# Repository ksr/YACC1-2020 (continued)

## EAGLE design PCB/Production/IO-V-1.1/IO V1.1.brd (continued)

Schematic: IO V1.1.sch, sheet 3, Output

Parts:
0, 1, 2, 3, 4, 5, 6, 7: LED5MM
HI: HTIL311A
IC4, IC9: 74273N; DIL20
IC6, IC11: 74LS10N; DIL14
IC7: 74LS00N; DIL14
LO: HTIL311A
OUT: LED5MM
R1, R3, R4, R5, R6, R7, R8, R9, R10: R-US_0207/10; 0207/10
TM1: 10k; TRIM-3386
X2: HD44780LCD-1602; LCD1602

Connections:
-B-RESET: IC4.1 (CLR), IC9.1 (CLR); also elsewhere on the board
DATA0: IC4.3 (D1), IC9.3 (D1), X2.7 (DB0); also elsewhere on the board
DATA1: IC4.4 (D2), IC9.4 (D2), X2.8 (DB1); also elsewhere on the board
DATA2: IC4.7 (D3), IC9.7 (D3), X2.9 (DB2); also elsewhere on the board
DATA3: IC4.8 (D4), IC9.8 (D4), X2.10 (DB3); also elsewhere on the board
DATA4: IC4.13 (D5), IC9.13 (D5), X2.11 (DB4); also elsewhere on the board
DATA5: IC4.14 (D6), IC9.14 (D6), X2.12 (DB5); also elsewhere on the board
DATA6: IC4.17 (D7), IC9.17 (D7), X2.13 (DB6); also elsewhere on the board
DATA7: IC4.18 (D8), IC9.18 (D8), X2.14 (DB7); also elsewhere on the board
GND: 0.K (C), 1.K (C), 2.K (C), 3.K (C), 4.K (C), 5.K (C), 6.K (C), 7.K (C), HI.5 (L-SI), HI.7 (GND), HI.8 (BI), IC4.10 (GND), IC6.7 (GND), IC7.7 (GND), IC9.10 (GND), IC11.7 (GND), LO.5 (L-SI), LO.7 (GND), LO.8 (BI), OUT.K (C), TM1.3 (E), X2.1 (VSS), X2.5 (RW), X2.16 (K); also elsewhere on the board
IO-SELDATA: IC6.2 (I1), IC6.9 (I0), IC11.2 (I1); also elsewhere on the board
IO-WR: IC6.1 (I0), IC6.11 (I2), IC11.1 (I0); also elsewhere on the board
LCD-ENABLE: IC6.10 (I1); also elsewhere on the board
LCD-REGISTER: X2.4 (RS); also elsewhere on the board
unnamed: OUT.A, R1.1
unnamed: 2.A, R5.1
unnamed: 3.A, R6.1
unnamed: 4.A, R7.1
unnamed: 0.A, R3.1
unnamed: 1.A, R4.1
unnamed: 5.A, R8.1
unnamed: 7.A, R10.1
unnamed: 6.A, R9.1
unnamed: IC4.19 (Q8), R10.2
unnamed: IC4.16 (Q7), R9.2
unnamed: IC4.15 (Q6), R8.2
unnamed: IC4.12 (Q5), R7.2
unnamed: IC4.9 (Q4), R6.2
unnamed: IC4.6 (Q3), R5.2
unnamed: IC4.5 (Q2), R4.2
unnamed: IC4.2 (Q1), R3.2
unnamed: HI.12 (D3), IC9.19 (Q8)
unnamed: IC7.3 (O), X2.6 (E)
unnamed: IC6.8 (O), IC7.1 (I0), IC7.2 (I1)
unnamed: IC4.11 (CLK), IC6.12 (O)
unnamed: TM1.2 (S), X2.3 (VO)
unnamed: HI.13 (D2), IC9.16 (Q7)
unnamed: HI.2 (D1), IC9.15 (Q6)
unnamed: HI.3 (D0), IC9.12 (Q5)
unnamed: IC9.9 (Q4), LO.12 (D3)
unnamed: IC9.6 (Q3), LO.13 (D2)
unnamed: IC9.5 (Q2), LO.2 (D1)
unnamed: IC9.2 (Q1), LO.3 (D0)
unnamed: IC9.11 (CLK), IC11.12 (O)
OUT: R1.2; also elsewhere on the board
SWITCH-LED: IC6.13 (I2); also elsewhere on the board
TIL311: IC11.13 (I2); also elsewhere on the board
VCC: HI.1 (LEDSUP), HI.14 (VCC), IC4.20 (VCC), IC6.14 (VCC), IC7.14 (VCC), IC9.20 (VCC), IC11.14 (VCC), LO.1 (LEDSUP), LO.14 (VCC), TM1.1 (A), X2.2 (VDD), X2.15 (A); also elsewhere on the board

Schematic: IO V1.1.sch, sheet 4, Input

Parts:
IC3: 74LS244N; DIL20
IC6: 74LS10N; DIL14
IN: M9040P
INPUT: PINHD-1X2; 1X02
S0, S1, S2, S3, S4, S5, S6, S7: M9040P

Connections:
DATA0: IC3.18 (Y1); also elsewhere on the board
DATA1: IC3.16 (Y2); also elsewhere on the board
DATA2: IC3.14 (Y3); also elsewhere on the board
DATA3: IC3.12 (Y4); also elsewhere on the board
DATA4: IC3.9 (Y1); also elsewhere on the board
DATA5: IC3.7 (Y2); also elsewhere on the board
DATA6: IC3.5 (Y3); also elsewhere on the board
DATA7: IC3.3 (Y4); also elsewhere on the board
GND: IC3.10 (GND), IC6.7 (GND), IN.3 (S), S0.3 (S), S1.3 (S), S2.3 (S), S3.3 (S), S4.3 (S), S5.3 (S), S6.3 (S), S7.3 (S); also elsewhere on the board
IN: INPUT.1; also elsewhere on the board
IO-RD: IC6.3 (I0); also elsewhere on the board
IO-SELDATA: IC6.4 (I1); also elsewhere on the board
unnamed: IC3.2 (A1), S0.2
unnamed: IC3.4 (A2), S1.2
unnamed: IC3.6 (A3), S2.2
unnamed: IC3.8 (A4), S3.2
unnamed: IC3.11 (A1), S4.2
unnamed: IC3.13 (A2), S5.2
unnamed: IC3.15 (A3), S6.2
unnamed: IC3.17 (A4), S7.2
unnamed: IC3.1 (G), IC3.19 (G), IC6.6 (O)
unnamed: IN.2, INPUT.2
SWITCH-LED: IC6.5 (I2); also elsewhere on the board
VCC: IC3.20 (VCC), IC6.14 (VCC), IN.1 (O), S0.1 (O), S1.1 (O), S2.1 (O), S3.1 (O), S4.1 (O), S5.1 (O), S6.1 (O), S7.1 (O); also elsewhere on the board

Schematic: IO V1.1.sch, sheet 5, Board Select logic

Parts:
DATA-ADDR: PINHD-2X8; 2X08
IC5: 74LS138N; DIL16
IC7: 74LS00N; DIL14
IC8: 74LS06N; DIL14
IC10: 74273N; DIL20
IO-ADDR: PINHD-2X8; 2X08
IO-ADDR-HL: PINHD-2X3; 2X03
RN2: RNX6; RN-7

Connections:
-B-RESET: IC10.1 (CLR); also elsewhere on the board
-IO-ADDRSEL: IC7.12 (I0), IC7.13 (I1), IO-ADDR.1, IO-ADDR.3, IO-ADDR.5, IO-ADDR.7, IO-ADDR.9, IO-ADDR.11, IO-ADDR.13, IO-ADDR.15
-IO-DATASEL: DATA-ADDR.1, DATA-ADDR.3, DATA-ADDR.5, DATA-ADDR.7, DATA-ADDR.9, DATA-ADDR.11, DATA-ADDR.13, DATA-ADDR.15, IC8.11 (I)
-IO-SEL0: DATA-ADDR.16, IC5.15 (Y0), IO-ADDR.16
-IO-SEL1: DATA-ADDR.14, IC5.14 (Y1), IO-ADDR.14
-IO-SEL2: DATA-ADDR.12, IC5.13 (Y2), IO-ADDR.12
-IO-SEL3: DATA-ADDR.10, IC5.12 (Y3), IO-ADDR.10
-IO-SEL4: DATA-ADDR.8, IC5.11 (Y4), IO-ADDR.8
-IO-SEL5: DATA-ADDR.6, IC5.10 (Y5), IO-ADDR.6
-IO-SEL6: DATA-ADDR.4, IC5.9 (Y6), IO-ADDR.4
-IO-SEL7: DATA-ADDR.2, IC5.7 (Y7), IO-ADDR.2
DATA0: IC10.3 (D1); also elsewhere on the board
DATA1: IC10.4 (D2); also elsewhere on the board
DATA2: IC10.7 (D3); also elsewhere on the board
DATA3: IC10.8 (D4); also elsewhere on the board
DATA4: IC10.13 (D5); also elsewhere on the board
DATA5: IC10.14 (D6); also elsewhere on the board
DATA6: IC10.17 (D7); also elsewhere on the board
DATA7: IC10.18 (D8); also elsewhere on the board
GND: IC5.5 (G2B), IC5.8 (GND), IC7.7 (GND), IC8.7 (GND), IC10.10 (GND), IO-ADDR-HL.1; also elsewhere on the board
IO-ADDR0: IC5.1 (A); also elsewhere on the board
IO-ADDR1: IC5.2 (B); also elsewhere on the board
IO-ADDR2: IC5.3 (C); also elsewhere on the board
IO-ADDR3: IO-ADDR-HL.2, IO-ADDR-HL.5; also elsewhere on the board
IO-SELDATA: IC8.10 (O), RN2.3; also elsewhere on the board
IO-WR: IC7.5 (I1); also elsewhere on the board
LCD-ENABLE: IC10.5 (Q2); also elsewhere on the board
LCD-REGISTER: IC10.6 (Q3); also elsewhere on the board
unnamed: IC5.4 (G2A), IO-ADDR-HL.3
unnamed: IC5.6 (G1), IO-ADDR-HL.4
unnamed: IC7.6 (O), IC10.11 (CLK)
unnamed: IC7.4 (I0), IC7.11 (O)
SWITCH-LED: IC10.2 (Q1); also elsewhere on the board
TIL311: IC10.19 (Q8); also elsewhere on the board
UART-A0: IC10.9 (Q4); also elsewhere on the board
UART-A1: IC10.12 (Q5); also elsewhere on the board
UART-A2: IC10.15 (Q6); also elsewhere on the board
UART-CS: IC10.16 (Q7); also elsewhere on the board
VCC: IC5.16 (VCC), IC7.14 (VCC), IC8.14 (VCC), IC10.20 (VCC), IO-ADDR-HL.6; also elsewhere on the board

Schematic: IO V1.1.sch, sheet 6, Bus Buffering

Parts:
IC8: 74LS06N; DIL14
RN2: RNX6; RN-7

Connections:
-B-RESET: IC8.8 (O), RN2.4; also elsewhere on the board
-IO-RD: IC8.1 (I); also elsewhere on the board
-IO-WR: IC8.3 (I); also elsewhere on the board
-RESET: IC8.5 (I); also elsewhere on the board
GND: IC8.7 (GND); also elsewhere on the board
IO-RD: IC8.2 (O), RN2.7; also elsewhere on the board
IO-WR: IC8.4 (O), RN2.6; also elsewhere on the board
RESET: IC8.6 (O), IC8.9 (I), RN2.5; also elsewhere on the board
VCC: IC8.14 (VCC), RN2.1; also elsewhere on the board

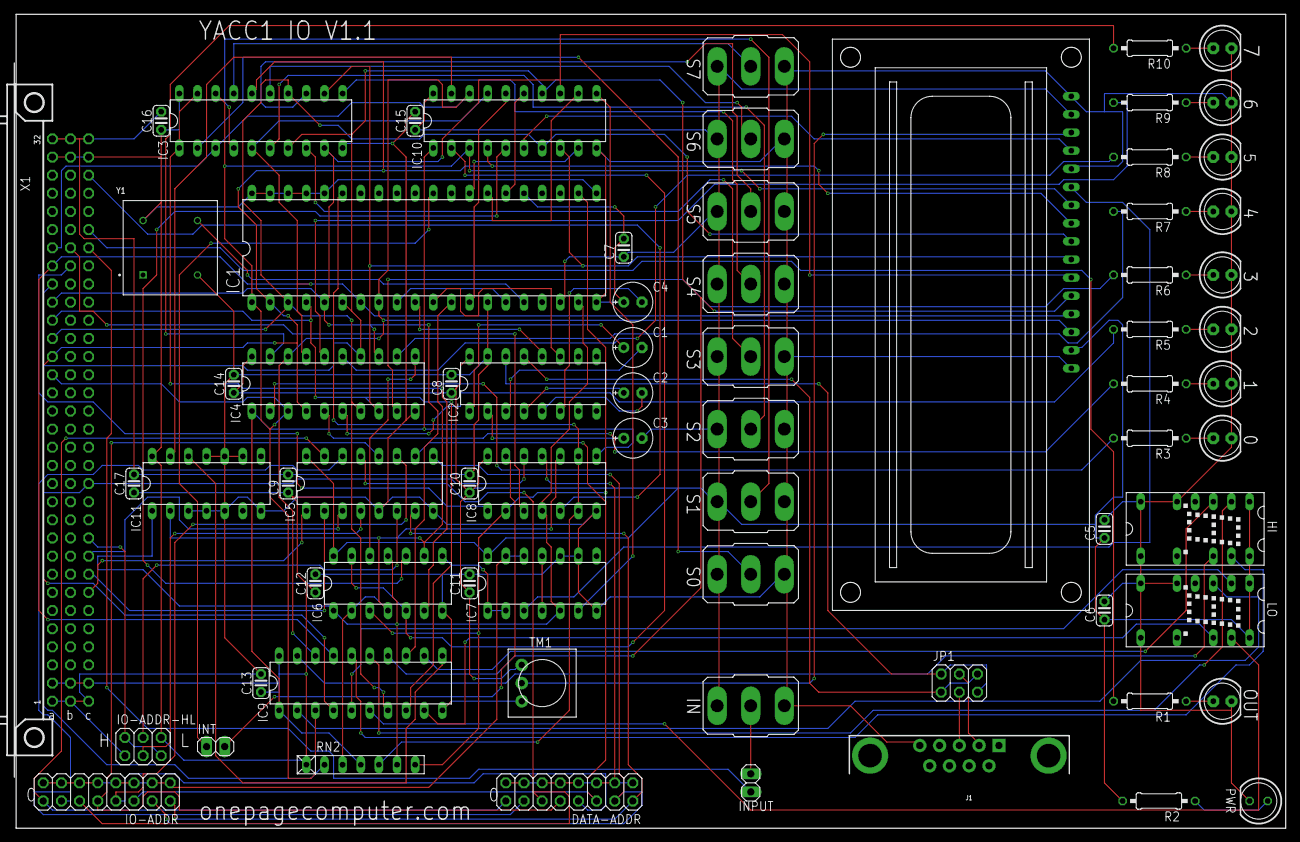
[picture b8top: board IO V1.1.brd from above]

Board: 2 copper layers, 177.8 x 114.0 mm, 71 parts (0 on the bottom side), 104 nets.

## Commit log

2020-08-23 Adding folder contents
2020-08-23 Some basic documentation
2020-08-23 Cleaning up old files
2020-08-23 cleaning up
2020-08-26 Adding data sheet
2020-08-28 Create clocker.ino
    Arduino app to assist in single stepping through microcode one line or one instruction at a time
2020-08-28 Index Register Board V1.1
    Modify so any data register can drive address bus
2020-08-28 Continuing to add new instrcutions
2020-08-28 Spilt code in multiple files
2020-08-29 Create file with single test
2020-08-29 Add opcodes
2020-08-29 Test code for RAM
2020-08-29 new ucode outputs
2020-09-01 Add 10 instruction at a time option
2020-09-01 New Index board with addition for each register to drive address bus
2020-09-01 New index register design, each register can drive address bug
2020-09-01 New memory card, switch to 8k eeprom add in tmp registers
2020-09-01 new memory card, switch to eeprom, add tmp register
2020-09-01 Ongoing development
2020-09-02 maintenance
2020-09-03 updates for new bus mem and register card
2020-09-03 Added INP instruction
2020-09-08 Notes for next rev
2020-09-08 build out test asm programs
2020-09-10 Add new instructions
2020-09-14 all updates around 3.2 bus update and new index card
2020-09-18 building out opcode set
2020-09-22 Added push pop ort andt. Several test functions. Basic Monitor (needs cleanup)
2020-09-22 Montior cleanup
2020-09-22 cleanup uart ready to xmit code
2020-09-22 Add eagle files
2020-09-22 Added BRNEQ (not tested), cleanup monitor
2020-09-22 testing gitignore
2020-09-22 Add link to arduino header file
    Place in Arduino/linraries/YACC (usually of of ~/Documents)
2020-09-22 Adding duplicate microcode line check
2020-09-24 cleanup production PCB area , add photos
2020-09-25 Added build notes for system and indivdual boards
2020-09-25 Added SUBT and BRUR opcodes
2020-09-25 Moved test board into production area
2020-09-25 added inva invert accumulator
2020-09-25 Test halt code
2020-09-26 Additional info imn notes
2020-09-26 rename original 1.0 index register
2020-09-26 remove old dissambler code
2020-09-26 documentation
2020-09-26 change extension
2020-09-26 spelling fix
2020-09-26 more cleanup and documentation
2020-09-26 fix naming
2020-09-26 updated & consolidated documentation
2020-09-26 Cleanup and document
2020-09-26 document and cleanup
2020-09-27 adding bus driver CLI reference
2020-10-06 Build images
2020-10-06 Increase label size
2020-10-06 add instructions
2020-10-06 clean up ALU codes
2020-10-06 add comments
2020-10-07 latest version testing moverr and jsrur
2020-10-07 Updated microcode, moverr and jsrur
2020-10-09 Fixed test file
2020-10-11 fix subt instrution - remove extra increment PC
2020-10-11 Fix JSR JSRUR RET - clear test-in line before end of microcode
2020-10-11 debugging
2020-10-11 skip duplicate microcode lines
2020-10-11 adding board layout PDFs to PCB production directories
2020-10-11 Lots of updates including Fill, Block Dump, Reg Dump
2020-10-11 add writecurrent line to endInstruction to clear buffer
2020-10-11 artifacts
2020-10-16 Converting for use on YACC
    Added pre tokenizer, seems to be working
2020-10-16 Testing out for YACC
2020-10-17 original code test bed
2020-10-17 working two pass version
2020-10-19 added add remove find line, prep. for edit 1 line at a. time
2020-10-20 adding Basic execution engine
2020-10-20 add .o files
2020-10-20 pre changing runtime find/add/free find linenume
2020-10-20 removed unused
2020-10-24 New YACC1-2020 emulator
2020-10-24 New emulator
2020-10-24 add pushr popr opcodes
2020-10-24 ubsic interpreter split into 2 passes
2020-10-25 fix pushr popr
2020-10-25 pre move basic to 0xe000
2020-10-25 add dump hex
2020-10-26 added for and gosub, assumes r8 and r9, cleanup dhex
2020-10-27 verify pushr popr
2020-10-27 add pushr popr
2020-10-27 add pushr popr and tests
2020-10-31 pre file split into montitor and basic interpreter
2020-10-31 update ignore
2020-10-31 Update assembler
2020-11-03 Cleanup
2020-11-04 Breakout basic and monitor code - monitor move mode to a mem variable - add tests
2020-11-04 create combined rom image from monitor and rom image
2020-11-04 add memory based load store opcodes - remove BRUSR opcode
2020-11-14 Snapshot with basic interpreter working
2020-11-19 Compare functioning mult16 add16 sub16 Lots of cleanup needed but big checkpoint
2020-11-20 Fix FOR-NEXT, FIX keyword search
2020-11-20 Cleanup commented out lines, add or16 and and16
2020-11-21 added itoa
2020-11-21 ADDED PEEK AND POKE
2020-11-21 INLINE basic command interpreter
2020-11-23 Next version of ALU to production
2020-11-23 Unary negative fix
2020-11-23 pre fix unary negative
2020-11-23 UNARY NEGATIVES
2020-11-25 adding inp outp in progress and some performance optimization reordering exe stmt tests
2020-11-29 more datasheets
2020-11-29 Rename Connector C3-C6, ADDR-REG-ID0-3
    Rename Connector C3-C6, ADDR-REG-ID0-3
2020-11-29 Deleted Not ready for production
2020-11-29 No longer used moved to old & obsolete
2020-11-29 Fix signals in bus
2020-11-29 cleanup bus names
2020-11-29 cleanup bus
2020-11-29 Cleanup Bus signals
2020-11-29 Never used
2020-11-29 Interrupt mgmt code and tests
2020-11-29 file cleanup
2020-12-02 v2.1 sequencer logic & memory
2020-12-02 development sequencer & alu
2020-12-02 missing rebuilt from pre github backup
2020-12-06 update subtract opcodes to new ALU design
2020-12-06 BOMs
2020-12-06 cleanup and prepare for 64 line microcode instructions
2020-12-06 no change
2020-12-17 change buad rate to 38400
2020-12-17 Change branch code to new sequencer design using -BRANCH-RD (lo and high combined)
2020-12-17 Updates to new sequecner but keeping 32 lines of microcode/ins
2020-12-25 add a second 512k bit eeprom to 328 chip
2020-12-25 new control signal definition on sequencer card
2020-12-25 64 lines of microcode per instruction, all 64 lines generated
2021-01-05 Add readme.md
2021-01-05 Cleanup memory card files
2021-01-05 changes for larger microcode
2021-03-18 cleaning up paths
2021-03-18 cleaning
2021-03-18 added photos and videos
2021-03-18 move eagle to utilties
2021-03-19 added photos
2021-03-19 more photos
2021-03-19 remove unused
2021-03-19 cleanup debug
2021-07-10 Cleanup
    Remove Hex and add in opcodes
2021-07-10 cleanup to calm down warning messages from compiler
2021-07-10 Version 1 of dip-switch memory board
2021-07-10 Clean branch code
2021-07-11 Move mem switch v1.0 into production
2021-08-29 12 inch 8 sided bus board
2021-08-29 Register based 16 byte memory card
2021-08-29 missed git sync of this card - 8 sided bus board file
2021-08-29 missed git sync - register based 16 byte memory card
2021-08-29 v1.1 16 byte switch based programmable ROM card
2021-08-29 8 sided bus board
2021-08-29 sync up
2021-08-31 fix instruction decode logic for larger address space
2021-08-31 convert to use opcodes not hardcoded hex
2021-08-31 add ON OFF basic commands and ability to break into a running basic program
2021-09-01 Add 3d printed files - first board spacers for octagon bus board
2021-09-01 remove unused code
2021-09-02 not working needs revert
